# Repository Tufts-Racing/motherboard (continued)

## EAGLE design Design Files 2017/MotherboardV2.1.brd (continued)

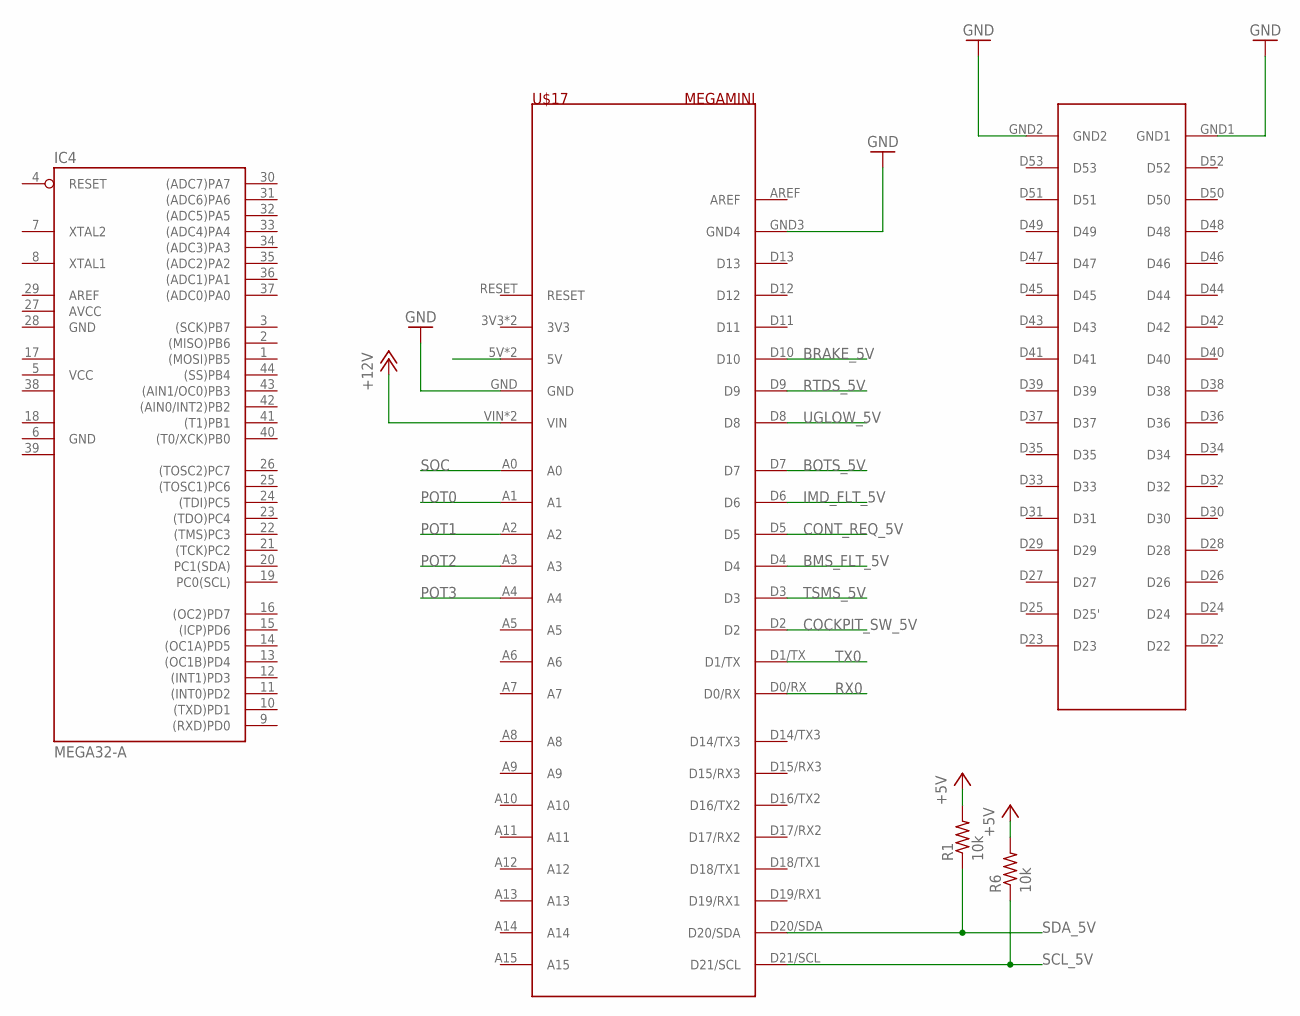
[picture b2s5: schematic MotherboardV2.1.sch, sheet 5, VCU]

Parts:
IC4: MEGA32-A; TQFP44
R1, R6: 10k; M0805
U$17: MEGAMINI

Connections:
+5V: R1.2, R6.2, U$17.5V, U$17.5V_2 (5V); also elsewhere on the board
+12V: U$17.VIN, U$17.VIN_2 (VIN); also elsewhere on the board
AVCC: IC4.27 (AVCC)
BMS_FLT_5V: U$17.D4; also elsewhere on the board
BOTS_5V: U$17.D7; also elsewhere on the board
BRAKE_5V: U$17.D10
COCKPIT_SW_5V: U$17.D2; also elsewhere on the board
CONT_REQ_5V: U$17.D5; also elsewhere on the board
GND: IC4.6 (GND), IC4.28 (GND), U$17.GND, U$17.GND1, U$17.GND2, U$17.GND3 (GND4); also elsewhere on the board
GND1: IC4.18 (GND1)
GND2: IC4.39 (GND2)
IMD_FLT_5V: U$17.D6; also elsewhere on the board
POT0: U$17.A1
POT1: U$17.A2
POT2: U$17.A3
POT3: U$17.A4
RTDS_5V: U$17.D9; also elsewhere on the board
RX0: U$17.D0/RX
SCL_5V: R6.1, U$17.D21/SCL; also elsewhere on the board
SDA_5V: R1.1, U$17.D20/SDA; also elsewhere on the board
SOC: U$17.A0; also elsewhere on the board
TSMS_5V: U$17.D3; also elsewhere on the board
TX0: U$17.D1/TX
UGLOW_5V: U$17.D8; also elsewhere on the board
VCC: IC4.5 (VCC)
VCC1: IC4.17 (VCC1)
VCC2: IC4.38 (VCC2)

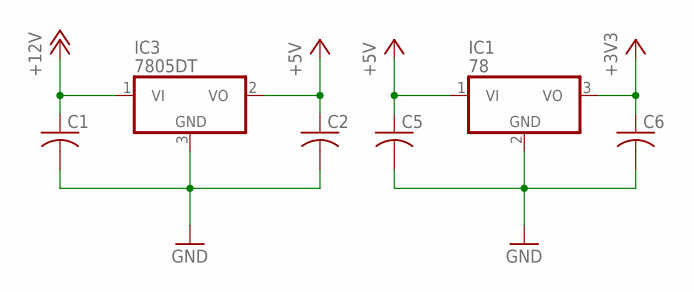
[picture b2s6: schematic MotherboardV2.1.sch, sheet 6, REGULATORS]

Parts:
C1, C2, C5, C6: C-USC0805K; C0805K
IC1: 78; D2PAK
IC3: 7805DT; TO252

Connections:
+3V3: C6.1, IC1.3 (VO)
+5V: C2.1, C5.1, IC1.1 (VI), IC3.2 (VO); also elsewhere on the board
+12V: C1.1, IC3.1 (VI); also elsewhere on the board
GND: C1.2, C2.2, C5.2, C6.2, IC1.2 (GND), IC3.3 (GND); also elsewhere on the board

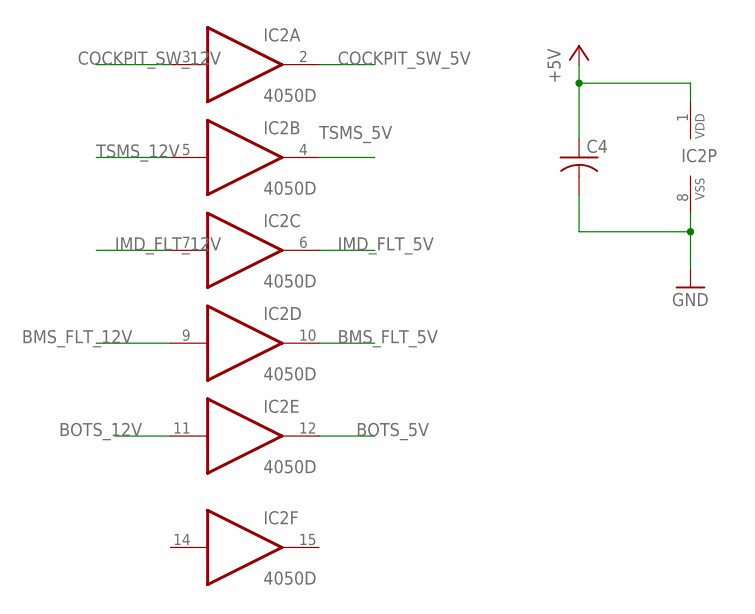
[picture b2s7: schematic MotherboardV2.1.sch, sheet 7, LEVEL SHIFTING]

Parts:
C4: C-US050-024X044; C050-024X044
IC2: 4050D; SO16

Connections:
+5V: C4.1, IC2.1 (VDD); also elsewhere on the board
BMS_FLT_5V: IC2.10 (O); also elsewhere on the board
BMS_FLT_12V: IC2.9 (I); also elsewhere on the board
BOTS_5V: IC2.12 (O); also elsewhere on the board
BOTS_12V: IC2.11 (I); also elsewhere on the board
COCKPIT_SW_5V: IC2.2 (O); also elsewhere on the board
COCKPIT_SW_12V: IC2.3 (I); also elsewhere on the board
GND: C4.2, IC2.8 (VSS); also elsewhere on the board
IMD_FLT_5V: IC2.6 (O); also elsewhere on the board
IMD_FLT_12V: IC2.7 (I); also elsewhere on the board
TSMS_5V: IC2.4 (O); also elsewhere on the board
TSMS_12V: IC2.5 (I); also elsewhere on the board

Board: 2 copper layers, 53 parts (0 on the bottom side), 48 nets, no tracks yet.

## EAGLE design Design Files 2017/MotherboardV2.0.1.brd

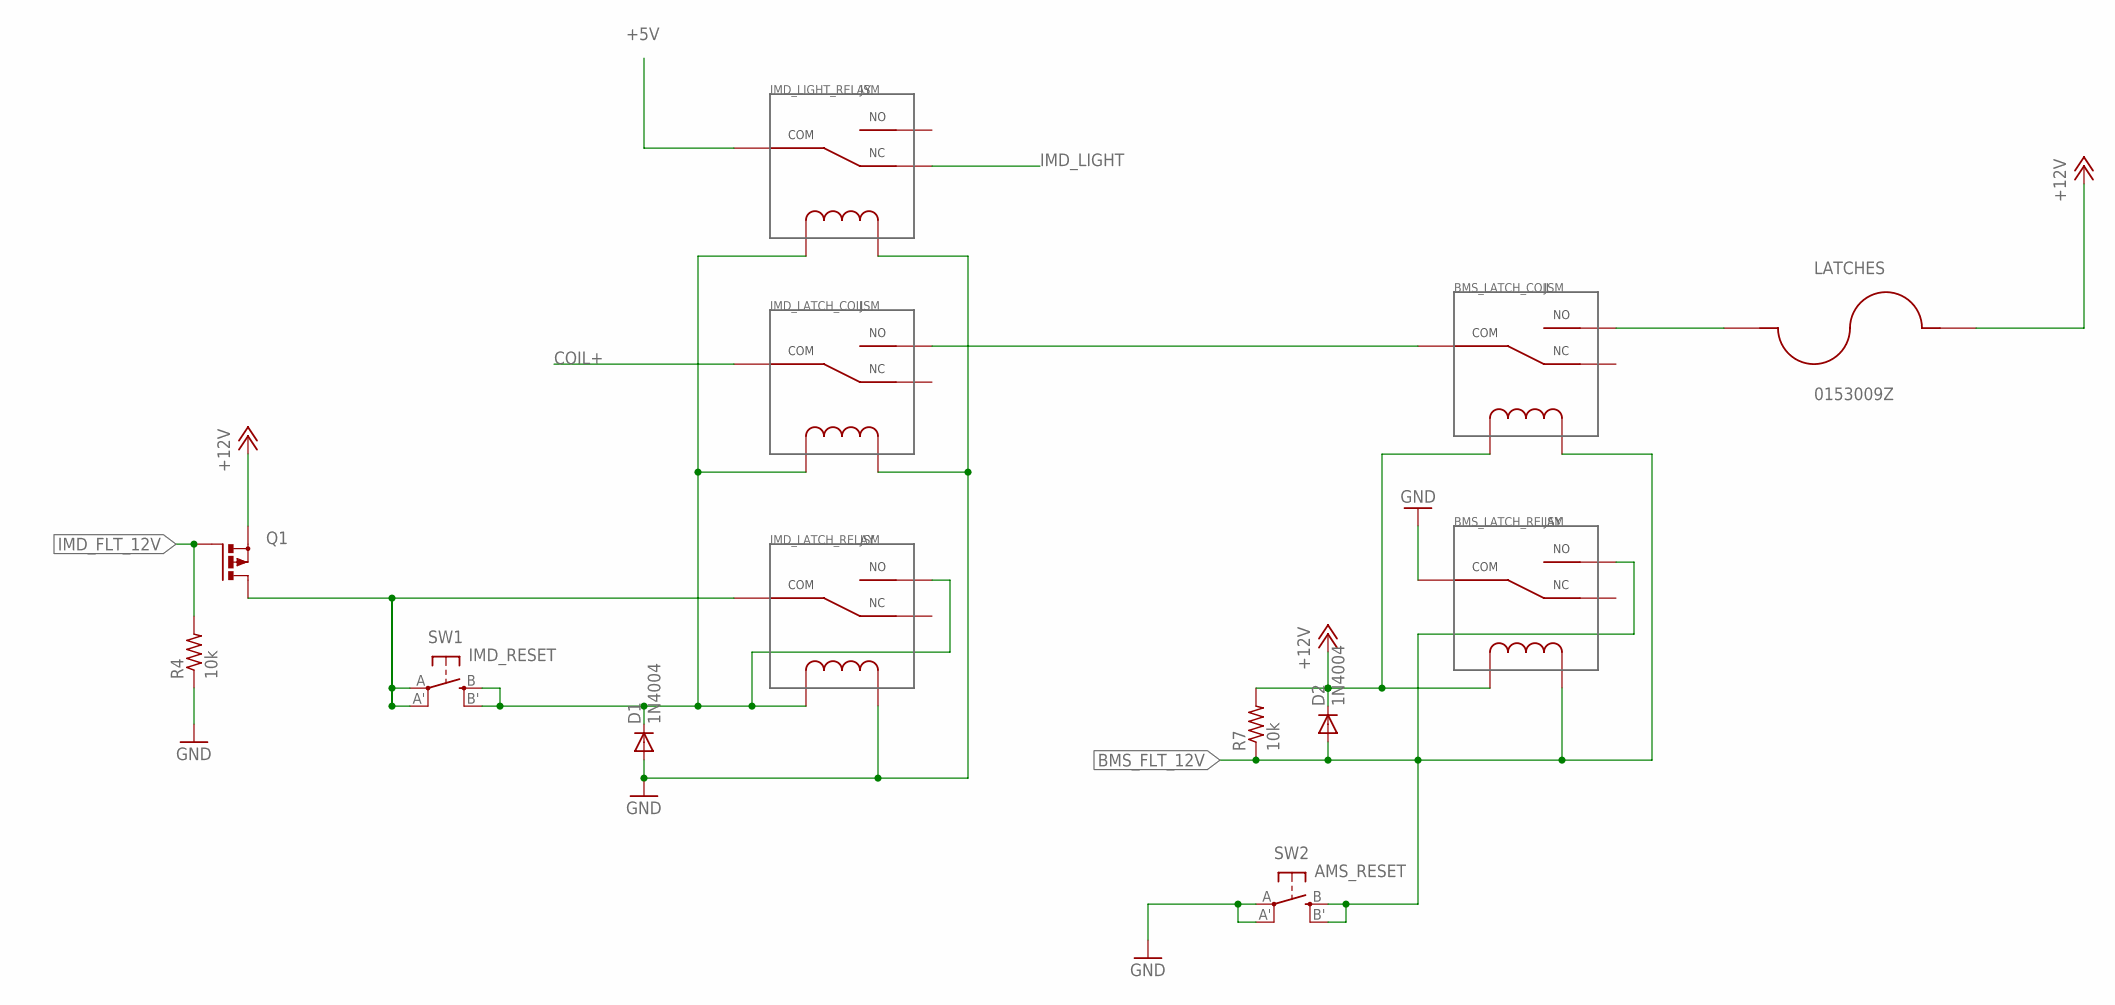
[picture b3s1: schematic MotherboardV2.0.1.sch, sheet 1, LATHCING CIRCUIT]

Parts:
BMS_LATCH_COIL: JSM; JS-M
BMS_LATCH_RELAY: JSM; JS-M
D1, D2: 1N4004; DO41-10
IMD_LATCH_COIL: JSM; JS-M
IMD_LATCH_RELAY: JSM; JS-M
IMD_LIGHT_RELAY: JSM; JS-M
LATCHES: 0153009Z; MINIFUSEHOLDER
Q1: PMOSFET_PTO220BV; TO220BV
R4, R7: 10k; 0207/9
SW1: IMD_RESET; EVQ-Q2
SW2: AMS_RESET; EVQ-Q2

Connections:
+5V: IMD_LIGHT_RELAY.COM; also elsewhere on the board
+12V: BMS_LATCH_COIL.COIL1, BMS_LATCH_RELAY.COIL1, D2.C, LATCHES.P$2, Q1.S, R7.2; also elsewhere on the board
BMS_FLT_12V: BMS_LATCH_COIL.COIL2, BMS_LATCH_RELAY.COIL2, BMS_LATCH_RELAY.NO, D2.A, R7.1, SW2.B (S), SW2.B' (S1); also elsewhere on the board
COIL+: IMD_LATCH_COIL.COM; also elsewhere on the board
GND: BMS_LATCH_RELAY.COM, D1.A, IMD_LATCH_COIL.COIL2, IMD_LATCH_RELAY.COIL2, IMD_LIGHT_RELAY.COIL2, R4.1, SW2.A, SW2.A' (P1); also elsewhere on the board
IMD_FLT_12V: Q1.G, R4.2; also elsewhere on the board
IMD_LATCH_SW1: IMD_LATCH_RELAY.COM, Q1.D, SW1.A, SW1.A' (P1); also elsewhere on the board
IMD_LATCH_SW2: D1.C, IMD_LATCH_COIL.COIL1, IMD_LATCH_RELAY.COIL1, IMD_LATCH_RELAY.NO, IMD_LIGHT_RELAY.COIL1, SW1.B (S), SW1.B' (S1); also elsewhere on the board
IMD_LIGHT: IMD_LIGHT_RELAY.NC
unnamed: BMS_LATCH_COIL.COM, IMD_LATCH_COIL.NO
unnamed: BMS_LATCH_COIL.NO, LATCHES.P$1

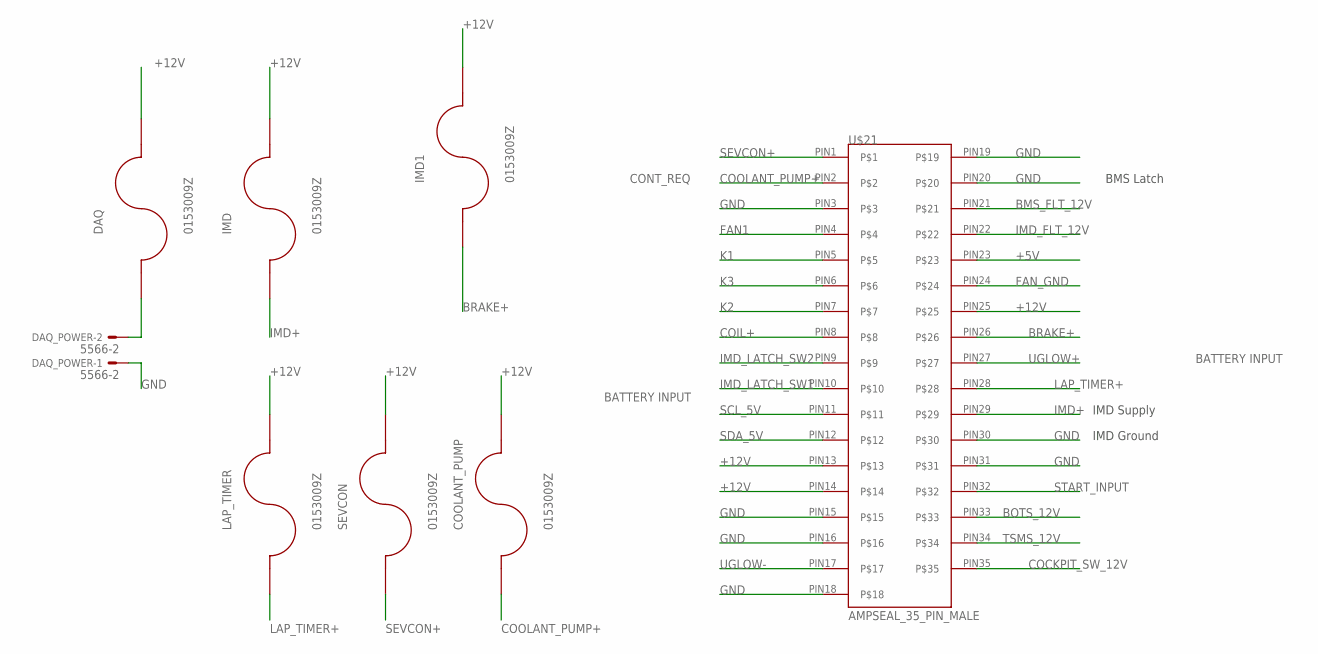
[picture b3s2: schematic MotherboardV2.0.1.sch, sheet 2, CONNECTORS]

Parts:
COOLANT_PUMP: 0153009Z; MINIFUSEHOLDER
DAQ: 0153009Z; MINIFUSEHOLDER
DAQ_POWER: 5566-2
IMD, IMD1: 0153009Z; MINIFUSEHOLDER
LAP_TIMER: 0153009Z; MINIFUSEHOLDER
SEVCON: 0153009Z; MINIFUSEHOLDER
U$21: AMPSEAL_35_PIN_MALE

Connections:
+5V: U$21.PIN23; also elsewhere on the board
+12V: COOLANT_PUMP.P$2, DAQ.P$2, IMD.P$2, IMD1.P$2, LAP_TIMER.P$2, SEVCON.P$2, U$21.PIN13, U$21.PIN14, U$21.PIN25; also elsewhere on the board
BMS_FLT_12V: U$21.PIN21; also elsewhere on the board
BOTS_12V: U$21.PIN33; also elsewhere on the board
BRAKE+: IMD1.P$1, U$21.PIN26
COCKPIT_SW_12V: U$21.PIN35; also elsewhere on the board
COIL+: U$21.PIN8; also elsewhere on the board
COOLANT_PUMP+: COOLANT_PUMP.P$1, U$21.PIN2
DAQ+: DAQ.P$1, DAQ_POWER.2
FAN1: U$21.PIN4; also elsewhere on the board
FAN_GND: U$21.PIN24; also elsewhere on the board
GND: DAQ_POWER.1, U$21.PIN3, U$21.PIN15, U$21.PIN16, U$21.PIN18, U$21.PIN19, U$21.PIN20, U$21.PIN30, U$21.PIN31; also elsewhere on the board
IMD+: IMD.P$1, U$21.PIN29
IMD_FLT_12V: U$21.PIN22; also elsewhere on the board
IMD_LATCH_SW1: U$21.PIN10; also elsewhere on the board
IMD_LATCH_SW2: U$21.PIN9; also elsewhere on the board
K1: U$21.PIN5; also elsewhere on the board
K2: U$21.PIN7; also elsewhere on the board
K3: U$21.PIN6; also elsewhere on the board
LAP_TIMER+: LAP_TIMER.P$1, U$21.PIN28
SCL_5V: U$21.PIN11; also elsewhere on the board
SDA_5V: U$21.PIN12; also elsewhere on the board
SEVCON+: SEVCON.P$1, U$21.PIN1
START_INPUT: U$21.PIN32; also elsewhere on the board
TSMS_12V: U$21.PIN34; also elsewhere on the board
UGLOW+: U$21.PIN27; also elsewhere on the board
UGLOW-: U$21.PIN17; also elsewhere on the board

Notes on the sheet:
BMS Latch
IMD Supply
IMD Ground
CONT_REQ
BATTERY INPUT

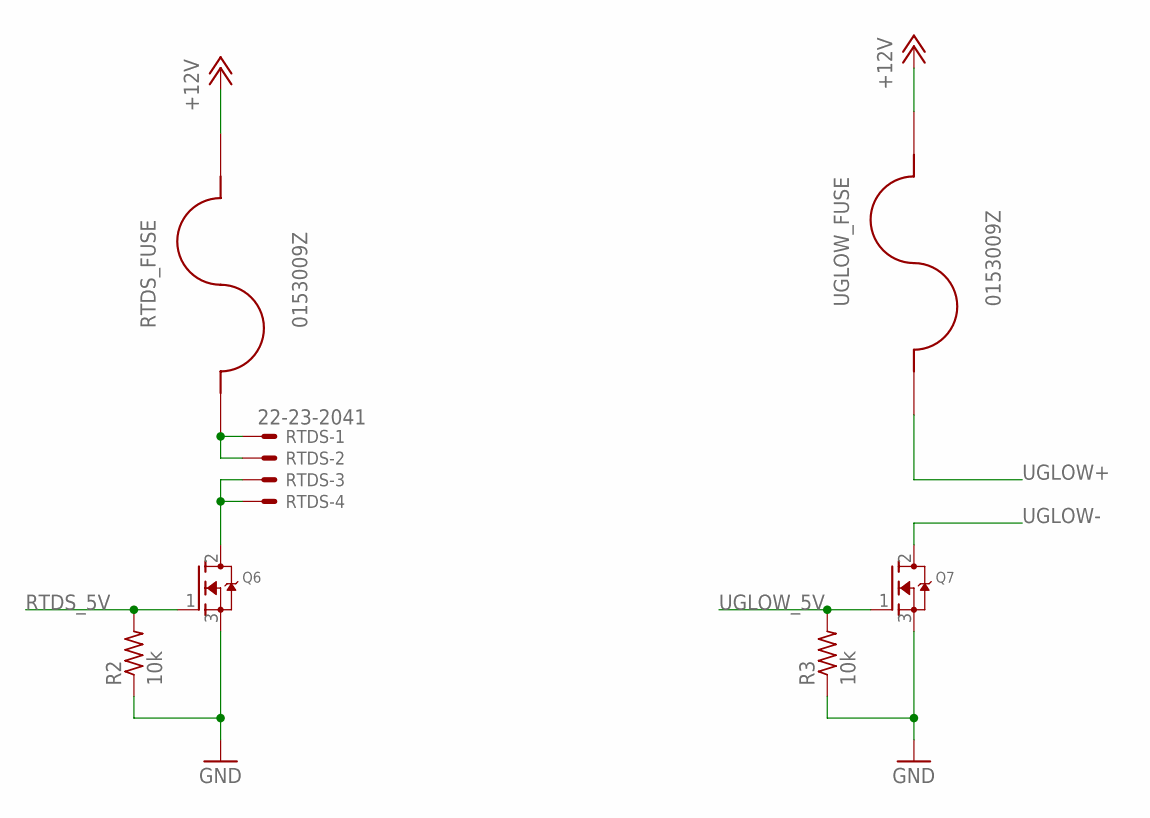
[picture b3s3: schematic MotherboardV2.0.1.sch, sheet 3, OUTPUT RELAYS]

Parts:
Q6, Q7: MOSFET-NGDS_TO220V; TO220V
R2, R3: 10k; 0207/9
RTDS: 22-23-2041; MPN 22-23-2041
RTDS_FUSE: 0153009Z; MINIFUSEHOLDER
UGLOW_FUSE: 0153009Z; MINIFUSEHOLDER

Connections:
+12V: RTDS_FUSE.P$2, UGLOW_FUSE.P$2; also elsewhere on the board
GND: Q6.3 (S), Q7.3 (S), R2.1, R3.1; also elsewhere on the board
unnamed: Q6.2 (D), RTDS.3, RTDS.4
unnamed: RTDS.1, RTDS.2, RTDS_FUSE.P$1
RTDS_5V: Q6.1 (G), R2.2; also elsewhere on the board
UGLOW+: UGLOW_FUSE.P$1; also elsewhere on the board
UGLOW-: Q7.2 (D); also elsewhere on the board
UGLOW_5V: Q7.1 (G), R3.2; also elsewhere on the board

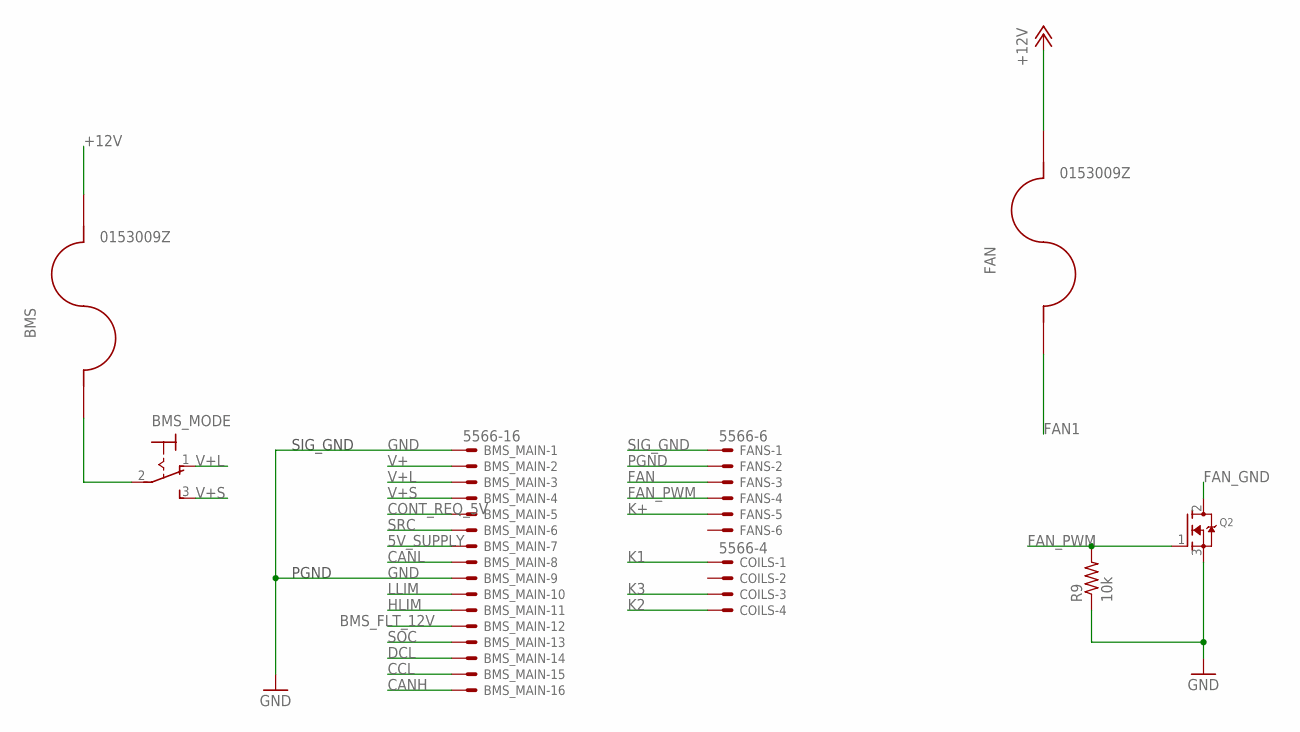
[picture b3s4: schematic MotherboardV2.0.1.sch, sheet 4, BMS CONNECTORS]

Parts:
BMS: 0153009Z; MINIFUSEHOLDER
BMS_MAIN: 5566-16
BMS_MODE: 320-916
COILS: 5566-4
FAN: 0153009Z; MINIFUSEHOLDER
FANS: 5566-6
Q2: MOSFET-NGDS_TO220V; TO220V
R9: 10k; 0207/9

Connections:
5V_SUPPLY: BMS_MAIN.7
+12V: BMS.P$2, FAN.P$2; also elsewhere on the board
BMS_FLT_12V: BMS_MAIN.12; also elsewhere on the board
CANH: BMS_MAIN.16
CANL: BMS_MAIN.8
CCL: BMS_MAIN.15
CONT_REQ_5V: BMS_MAIN.5; also elsewhere on the board
DCL: BMS_MAIN.14
FAN: FANS.3
FAN1: FAN.P$1; also elsewhere on the board
FAN_GND: Q2.2 (D); also elsewhere on the board
FAN_PWM: FANS.4, Q2.1 (G), R9.2
GND: BMS_MAIN.1, BMS_MAIN.9, Q2.3 (S), R9.1; also elsewhere on the board
HLIM: BMS_MAIN.11
K1: COILS.1; also elsewhere on the board
K2: COILS.4; also elsewhere on the board
K3: COILS.3; also elsewhere on the board
K+: FANS.5
LLIM: BMS_MAIN.10
unnamed: BMS.P$1, BMS_MODE.2
PGND: FANS.2
SIG_GND: FANS.1
SOC: BMS_MAIN.13; also elsewhere on the board
SRC: BMS_MAIN.6
V+: BMS_MAIN.2
V+L: BMS_MAIN.3, BMS_MODE.1 (O)
V+S: BMS_MAIN.4, BMS_MODE.3 (S)

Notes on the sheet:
SIG_GND
PGND

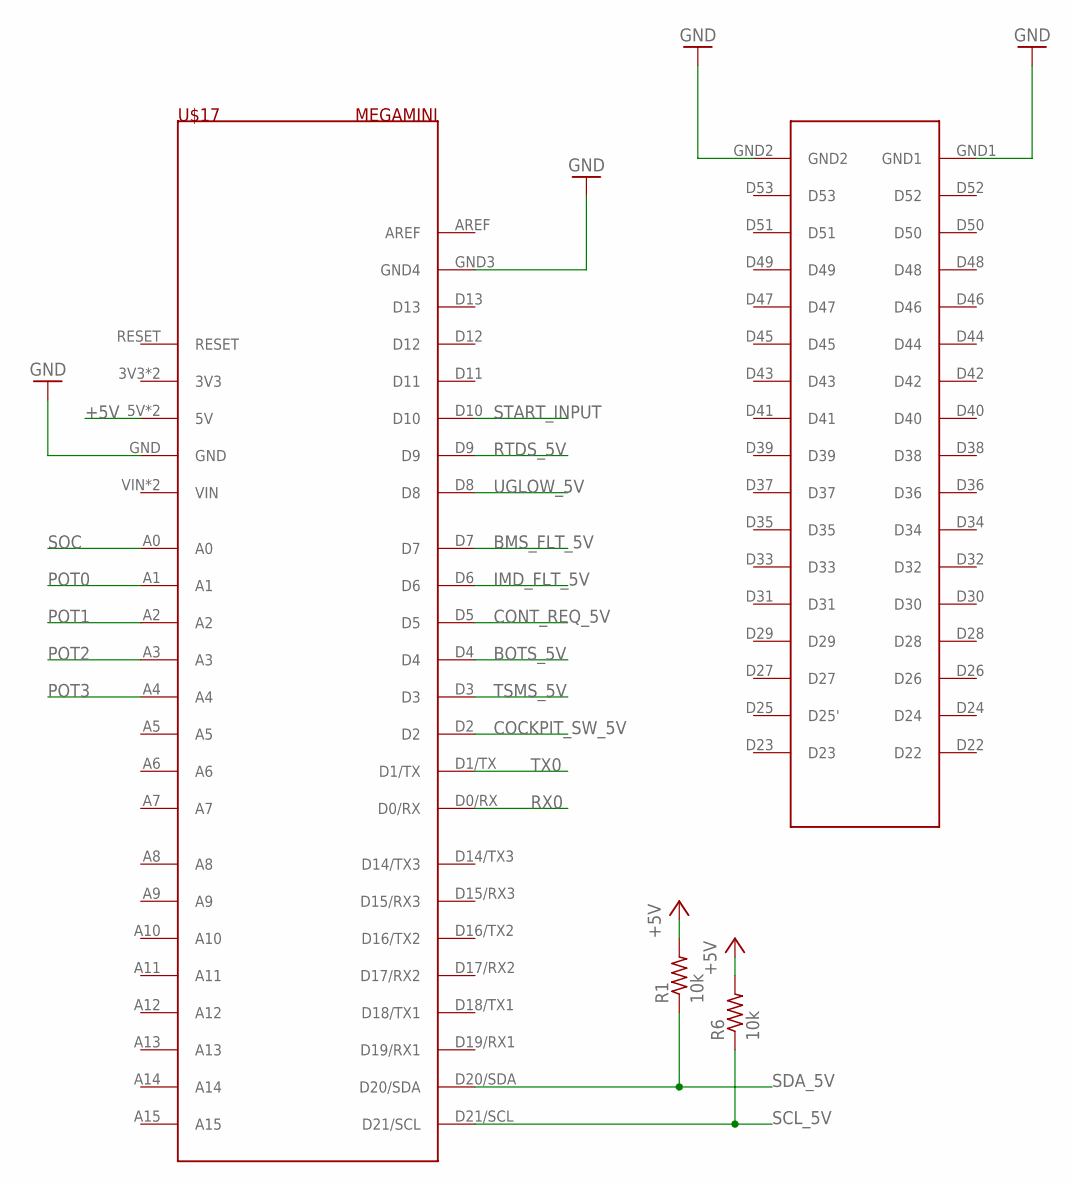
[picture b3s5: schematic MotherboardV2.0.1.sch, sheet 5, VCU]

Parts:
R1, R6: 10k; 0207/9
U$17: MEGAMINI

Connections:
+5V: R1.2, R6.2, U$17.5V, U$17.5V_2 (5V); also elsewhere on the board
BMS_FLT_5V: U$17.D7; also elsewhere on the board
BOTS_5V: U$17.D4; also elsewhere on the board
COCKPIT_SW_5V: U$17.D2; also elsewhere on the board
CONT_REQ_5V: U$17.D5; also elsewhere on the board
GND: U$17.GND, U$17.GND1, U$17.GND2, U$17.GND3 (GND4); also elsewhere on the board
IMD_FLT_5V: U$17.D6; also elsewhere on the board
POT0: U$17.A1
POT1: U$17.A2
POT2: U$17.A3
POT3: U$17.A4
RTDS_5V: U$17.D9; also elsewhere on the board
RX0: U$17.D0/RX
SCL_5V: R6.1, U$17.D21/SCL; also elsewhere on the board
SDA_5V: R1.1, U$17.D20/SDA; also elsewhere on the board
SOC: U$17.A0; also elsewhere on the board
START_INPUT: U$17.D10; also elsewhere on the board
TSMS_5V: U$17.D3; also elsewhere on the board
TX0: U$17.D1/TX
UGLOW_5V: U$17.D8; also elsewhere on the board

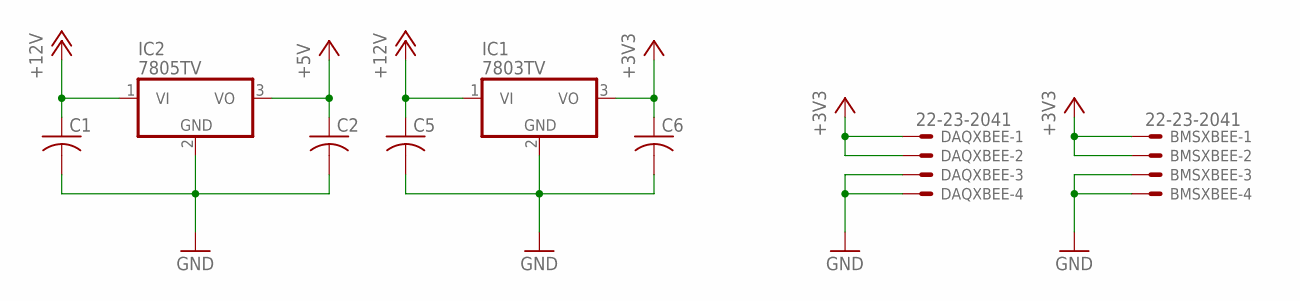
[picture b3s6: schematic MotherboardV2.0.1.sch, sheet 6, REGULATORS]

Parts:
BMSXBEE: 22-23-2041
C1, C2, C5, C6: C-US050-024X044; C050-024X044
DAQXBEE: 22-23-2041
IC1: 7803TV; TO220V
IC2: 7805TV; TO220V

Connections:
+3V3: BMSXBEE.1, BMSXBEE.2, C6.1, DAQXBEE.1, DAQXBEE.2, IC1.3 (VO)
+5V: C2.1, IC2.3 (VO); also elsewhere on the board
+12V: C1.1, C5.1, IC1.1 (VI), IC2.1 (VI); also elsewhere on the board
GND: BMSXBEE.3, BMSXBEE.4, C1.2, C2.2, C5.2, C6.2, DAQXBEE.3, DAQXBEE.4, IC1.2 (GND), IC2.2 (GND); also elsewhere on the board

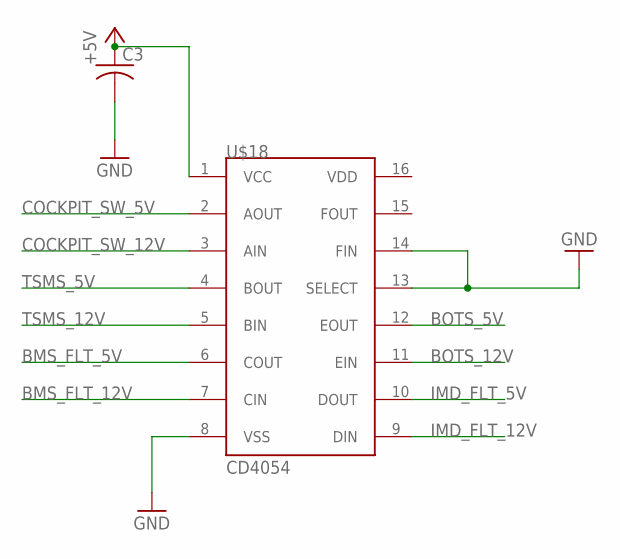
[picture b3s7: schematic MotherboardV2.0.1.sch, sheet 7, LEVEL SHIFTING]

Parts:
C3: C-US050-024X044; C050-024X044
U$18: CD4054; DIL16

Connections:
+5V: C3.1, U$18.1 (VCC); also elsewhere on the board
BMS_FLT_5V: U$18.6 (COUT); also elsewhere on the board
BMS_FLT_12V: U$18.7 (CIN); also elsewhere on the board
BOTS_5V: U$18.12 (EOUT); also elsewhere on the board
BOTS_12V: U$18.11 (EIN); also elsewhere on the board
COCKPIT_SW_5V: U$18.2 (AOUT); also elsewhere on the board
COCKPIT_SW_12V: U$18.3 (AIN); also elsewhere on the board
GND: C3.2, U$18.8 (VSS), U$18.13 (SELECT), U$18.14 (FIN); also elsewhere on the board
IMD_FLT_5V: U$18.10 (DOUT); also elsewhere on the board
IMD_FLT_12V: U$18.9 (DIN); also elsewhere on the board
TSMS_5V: U$18.4 (BOUT); also elsewhere on the board
TSMS_12V: U$18.5 (BIN); also elsewhere on the board

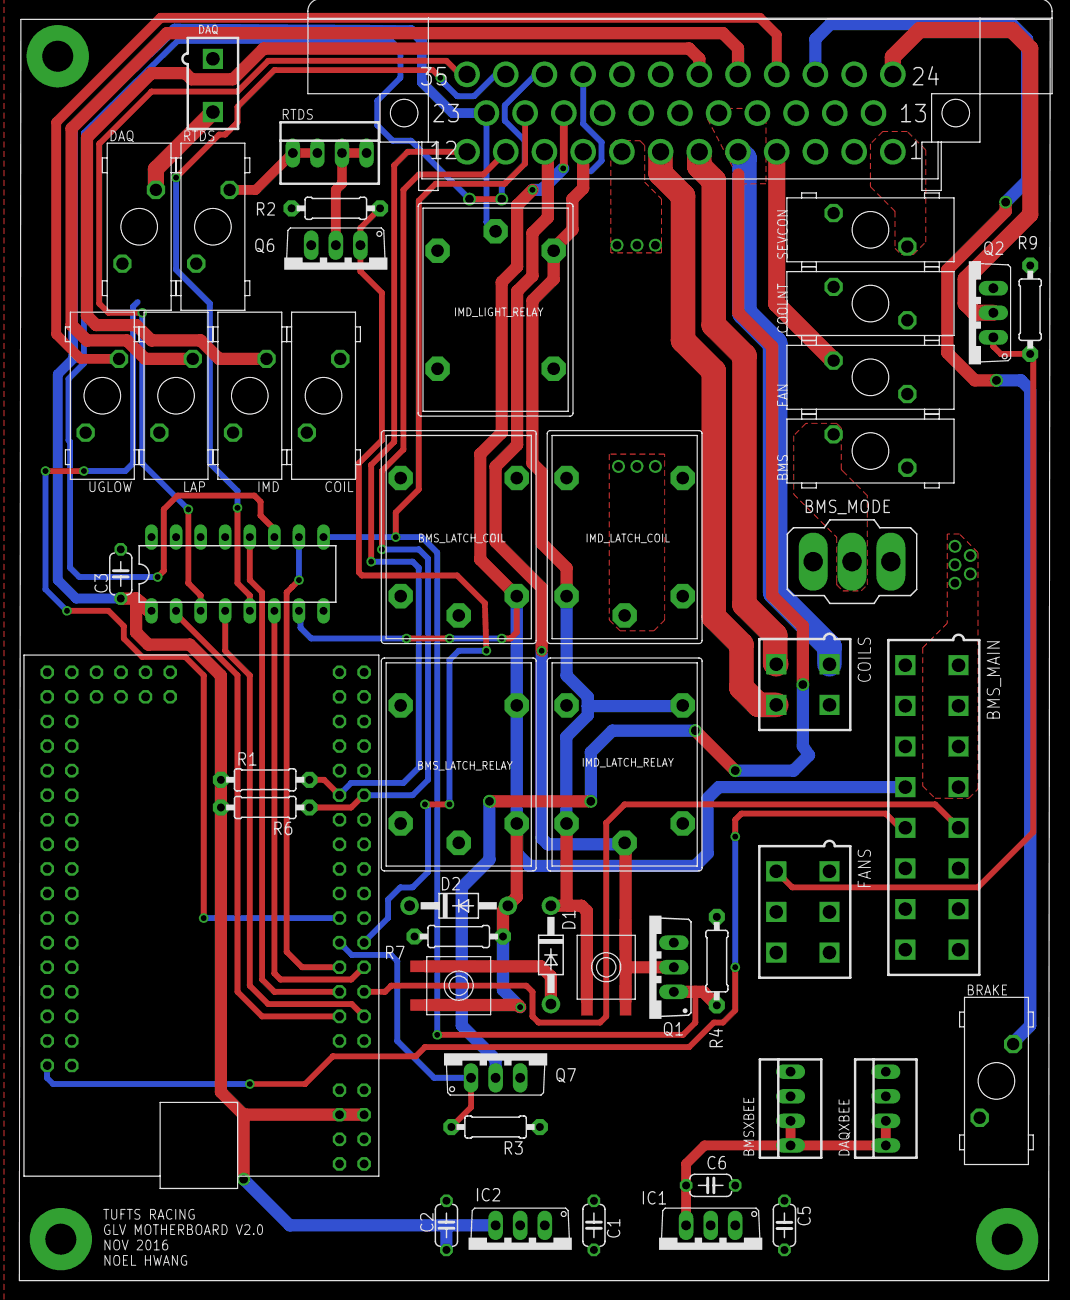
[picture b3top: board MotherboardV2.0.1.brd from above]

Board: 2 copper layers, 106.5 x 130.3 mm, 49 parts (0 on the bottom side), 45 nets.

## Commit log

2017-03-01 :boom::camel: Added .gitattributes
2017-03-01 Revert ":boom::camel: Added .gitattributes"
    This reverts commit f61a6a10b7456537d0813d11b2f9fc6429e065e7.
2017-03-01 v1.0
2017-03-01 Added Design Files
2017-03-01 Removed 2.1 files to slip
2017-03-01 Branch
2017-03-01 Cleanup
2017-03-08 Code edit and added pins file
2017-03-12 Driver Reset and drive direction
    Added Cockpit switch and drive direction logic
2017-03-13 Working Cockpit Switch Reset
    Needed pulldown on shutdown loop via an AIR. Drive DIR still floating
    because no Sevcon connected.
2017-03-22 RTDS Working
    Initialized RTDS Pin
2017-04-21 Fixed Pins for Motherboard Rev 2.0.3 Add direction read from steering wheel
2017-04-21 Direction Controls
2017-05-01 fixed serial comm w/ steering wheel
2017-10-16 Added design files 2018 with latest version of eagle files
2017-10-30 Fixed Sevcon Fault
2017-11-08 Names & Syntax
    Changed names to be more easily read/understood
    Changed Syntax to be continuous/easier to read
2017-11-20 Fixes for extended compiler bugs
    Created constant unsigned long for start duration
2018-03-28 Updated Code to for Broken out Atmega328p
2019-03-14 Cleaned up mobo code
    Unnecessary lines were removed and logic was updated to make code more readable.
